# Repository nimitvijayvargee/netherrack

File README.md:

# netherrack
A Compute Module 5 Carrier board to use as a minecraft server!
This is a project that I made once the minecraft server plans began to leave the group chat. I initially planned on using it for minecraft, but the applications can vary from home server, NAS to photo server. \
I plan to use a CM5 board with 4GB RAM. While I did plan on using a no emmc and no wireless module, I had to go for a 32GB and Wireless module because of availability. \
I plan to use a 256GB NVMe SSD for storage, which can be swapped out because of the inbuilt M.2 PCIe port. \
I also plan on adding some IO including USB and HDMI for debug or when I want to use it as a desktop. \
The board is designed to be mounted vertically, with the ports on the side and an acrylic panel on the front, giving it a retro green motherboard with a modern front panel look. \

 \

# BOM
|Item            |Link                                                                          |Cost|
|----------------|------------------------------------------------------------------------------|----|
|PCB + Assembly  |https://pcbpower.com/                                                         |140 |
|USB Stacked Port|https://mou.sr/3H7Itof/                                                       |4   |
|Magjack port    |https://mou.sr/4lZehuO/                                                       |10  |
|CM5 4GB 32GB    |https://www.fabtolab.com/raspberry-pi-compute-module-5/                       |95  |
|Case            |Print Legion                                                                  |    |
|NVMe SSD        |https://www.amazon.in/EVM-Internal-1800MB-EVMNV-256GB/dp/B09F6DNLBD/          |21  |
|Mounting Screws |https://quartzcomponents.com/products/m2-5-25mm-bolt-mounting-screw-pack-of-4/|3   |
|Mounting Inserts|https://www.amazon.in/Pro3D-Brass-Threaded-Round-Insert/dp/B0CZ44JWF9/        |3   |
|Acrylic Panel   |https://robu.in/ (From self)                                                  |    |
|TOTAL           |                                                                              |276 |

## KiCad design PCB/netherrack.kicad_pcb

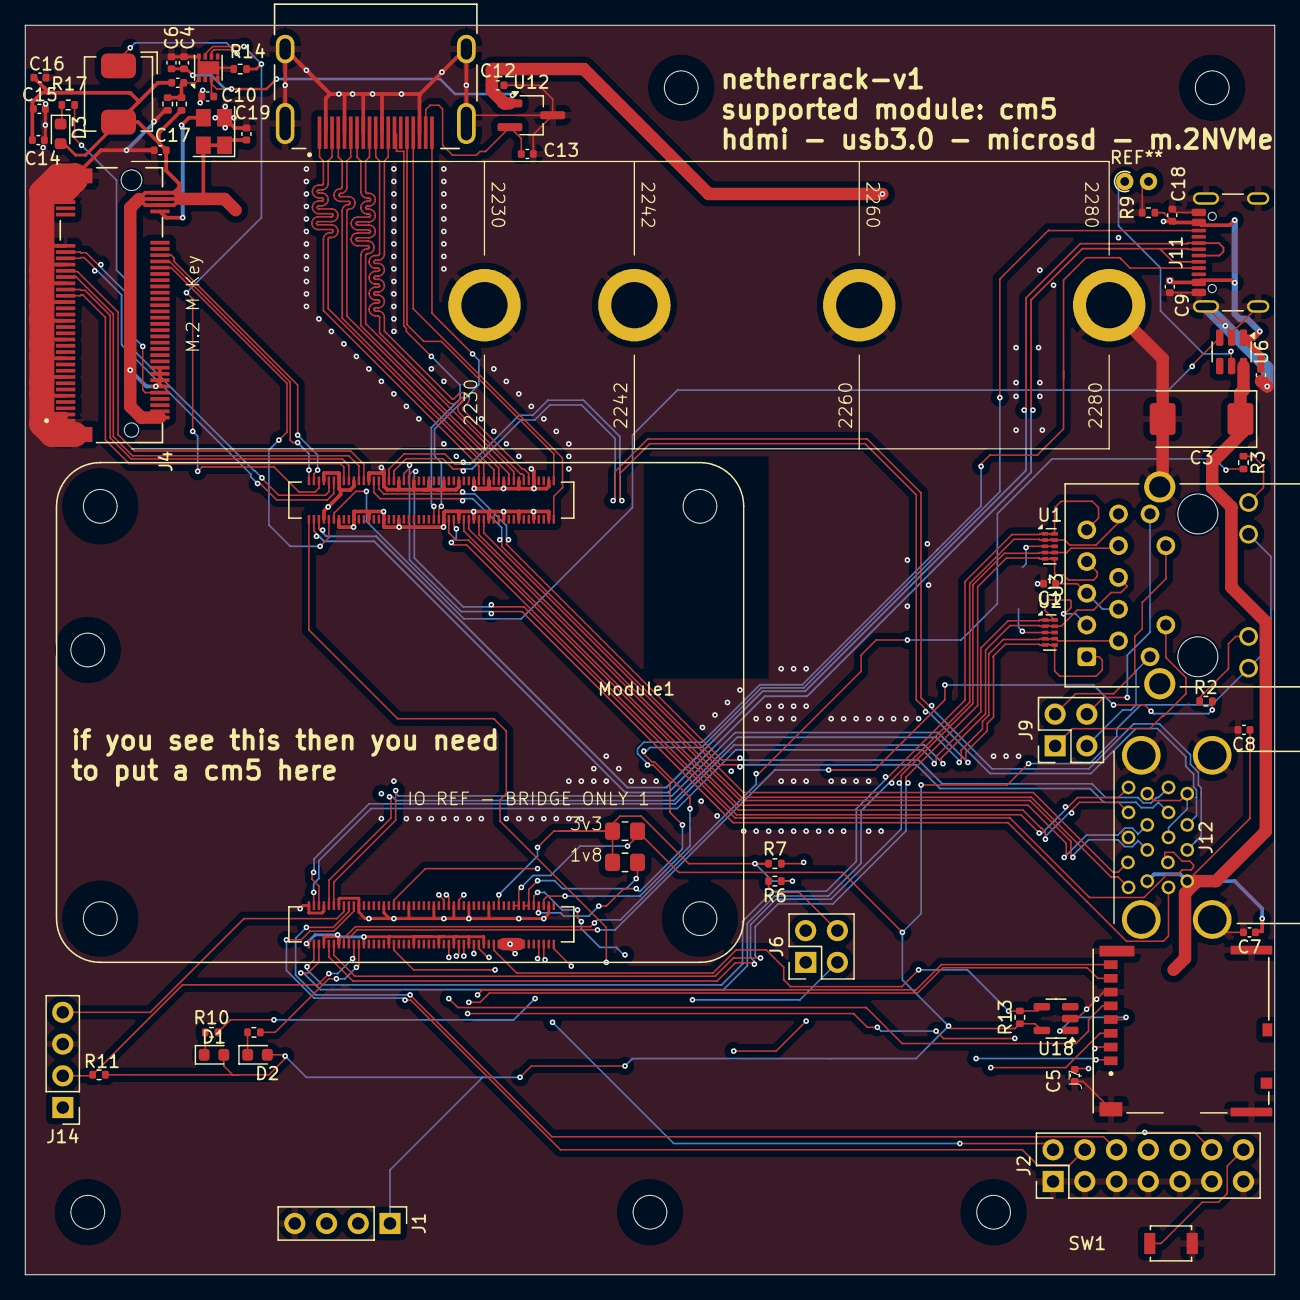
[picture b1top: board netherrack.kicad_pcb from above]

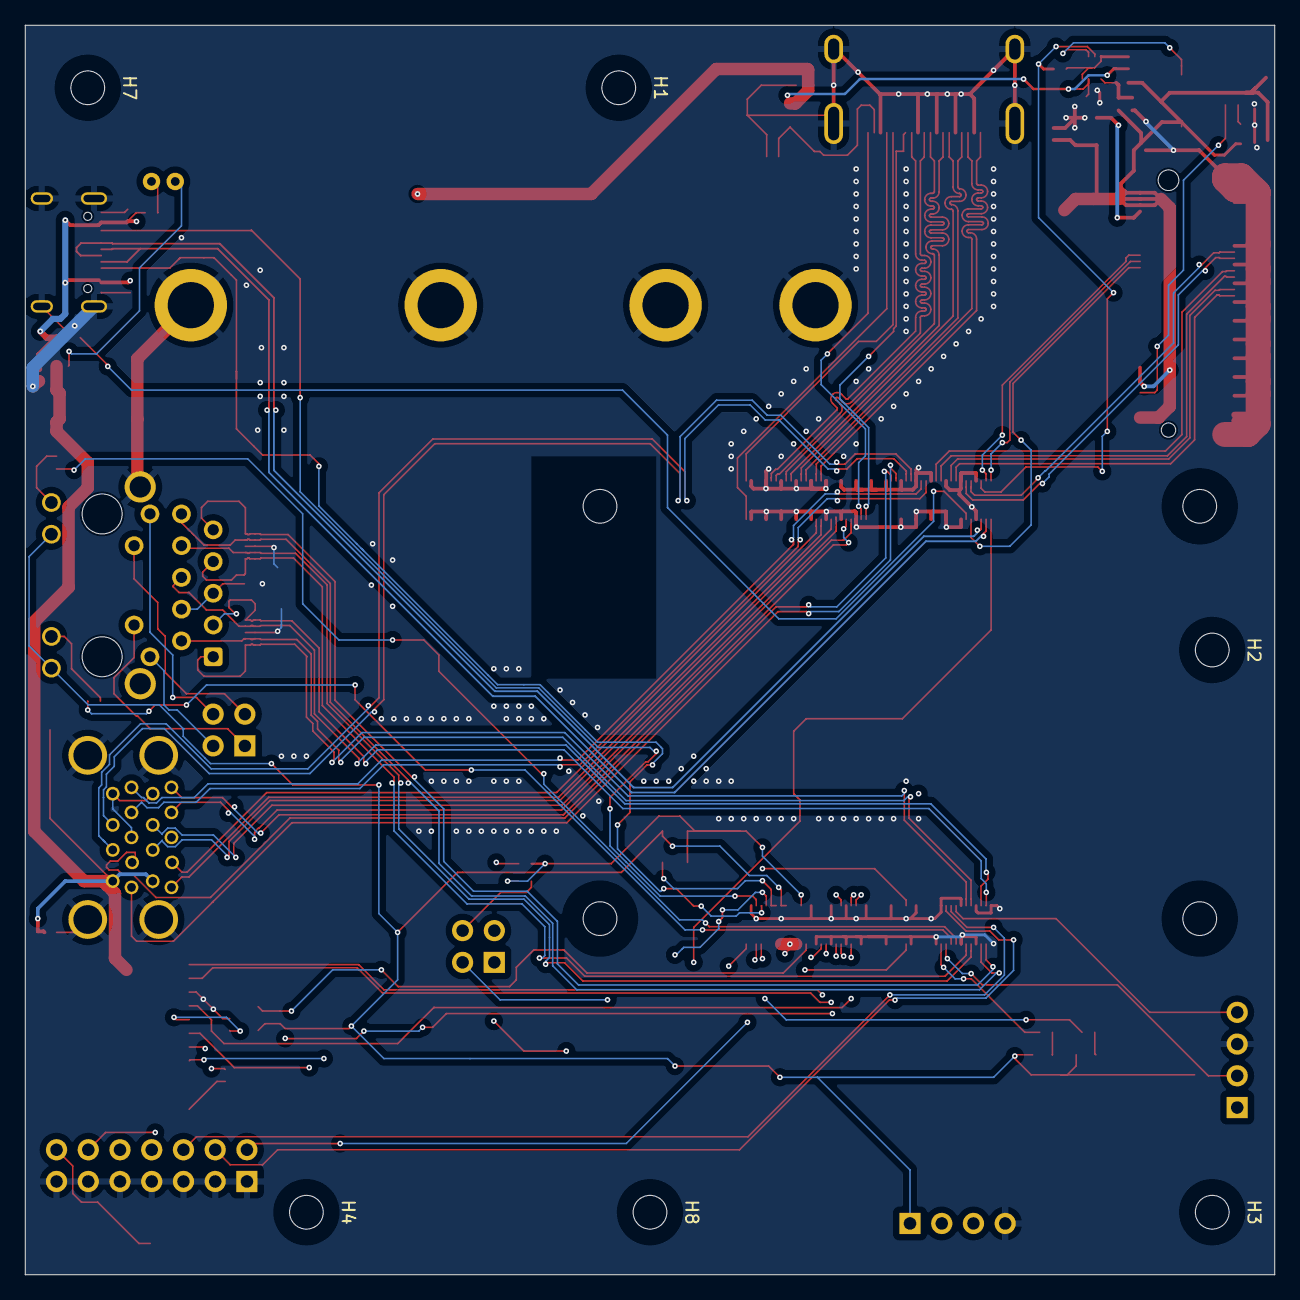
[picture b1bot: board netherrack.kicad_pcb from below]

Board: 4 copper layers, 100.0 x 100.0 mm, 64 parts (6 on the bottom side), 95 nets.

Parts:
C1, C9, C10, C12, C13, C18, C19: 100n; C_0402_1005Metric
C2, C4, C5, C6, C7, C8, C14, C15, C16, C17: 10u; C_0402_1005Metric
C3: 100uF; CP_EIA-7343-31_Kemet-D
C11: 4.7nF; C_0402_1005Metric
D1: LED Red; LED_0603_1608Metric
D2: LED Green; LED_0603_1608Metric
D3: LED; LED_0603_1608Metric
H1, H2, H3, H4, H7, H8: MountingHole; MountingHole_2.7mm_M2.5_DIN965
J1: Conn_01x04; PinHeader_1x04_P2.54mm_Vertical
J2: Conn_02x07_Odd_Even; PinHeader_2x07_P2.54mm_Vertical
J4: Bus_M.2_Socket_M; M.2 M Key socket
J6, J9: THD-02-R; PinHeader_2x02_P2.54mm_Vertical
J7: Micro_SD_Card_Det; SDCARD_MOLEX_503398-1892
J11: USB_C_Receptacle_USB2.0; USB_C_Receptacle_GCT_USB4105-xx-A_16P_TopMnt_Horizontal
J12: USB3_A; MTCONN_UBAF30-D2011
J14: JST_SHBM04B-SRSS-TB; PinHeader_1x04_P2.54mm_Vertical
J22: 690-019-298-412; EDAC 690-019-298-412
L1: 2.2uH; L_Bourns_SRP5030CC
Module1: ComputeModule5-CM5; Raspberry-Pi-5-Compute-Module
R1, R10, R17: 1k; R_0402_1005Metric
R2, R3: 470R; R_0402_1005Metric
R4: nf; R_0805_2012Metric_Pad1.20x1.40mm_HandSolder
R5: 0R; R_0805_2012Metric_Pad1.20x1.40mm_HandSolder
R6, R7, R9, R16: 2.2K 1%; R_0402_1005Metric
R11, R13, R15: 10K 1%; R_0402_1005Metric
R14: 100K 1%; R_0402_1005Metric
SW1: Right angle Tact button; SW_SPST_B3U-1000P
U1, U2: TPD4EUSB30; USON-10_2.5x1.0mm_P0.5mm
U3: MagJack-A70-112-331N126; TRJG0926HENL
U6: AP22653W6; SOT-23-6
U7: ASEK-32.768KHZ-L-R-T; Crystal_SMD_3225-4Pin_3.2x2.5mm
U8: AP3441SHE-7B; DFN-8-1EP_2x2mm_P0.5mm_EP1.05x1.75mm
U12: RT9742SNGV; TSOT-23_HandSoldering
U18: RT9742GGJ5; SOT-23-5

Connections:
/+3.3v: D1.2 (A), D2.2 (A), J1.1, Module1.84 (+3.3v_(Output)), Module1.86 (+3.3v_(Output)), R5.1, R11.1, R13.1, U3.15 (LEDY_A), U3.17 (LEDG_A), U18.5 (IN)
/+5v: C2.1, C4.1, C6.1, C9.1, C10.1, C12.1, C18.1, J11.A4 (VBUS), J11.A9 (VBUS), J11.B4 (VBUS), J11.B9 (VBUS), J14.1, Module1.77 (+5v_(Input)), Module1.79 (+5v_(Input)), Module1.81 (+5v_(Input)), Module1.83 (+5v_(Input)), Module1.85 (+5v_(Input)), Module1.87 (+5v_(Input)), R9.1, U6.1 (IN), U8.3 (VIN), U12.1 (IN)
/CC1: J11.A5 (CC1), Module1.94 (CC1)
/CC2: J11.B5 (CC2), Module1.96 (CC2)
/GPIO (Ethernet, SD_CARD for CM5L)/+1.8v: Module1.88 (+1.8v_(Output)), Module1.90 (+1.8v_(Output)), R4.1
/GPIO (Ethernet, SD_CARD for CM5L)/EEPROM_nWP: J2.4, Module1.20 (EEPROM_nWP)
/GPIO (Ethernet, SD_CARD for CM5L)/ETH_LEDG: Module1.17 (Ethernet_nLED2(3.3v)), R2.2
/GPIO (Ethernet, SD_CARD for CM5L)/ETH_LEDY: Module1.15 (Ethernet_nLED3(3.3v)), R3.2
/GPIO (Ethernet, SD_CARD for CM5L)/GPIO2: J1.2, Module1.58 (GPIO2)
/GPIO (Ethernet, SD_CARD for CM5L)/GPIO3: J1.3, Module1.56 (GPIO3)
/GPIO (Ethernet, SD_CARD for CM5L)/GPIO_VREF: Module1.78 (GPIO_VREF(1.8v/3.3v_Input)), R4.2, R5.2, R6.1, R7.1
/GPIO (Ethernet, SD_CARD for CM5L)/ID_SC: J6.1, Module1.35 (ID_SC)
/GPIO (Ethernet, SD_CARD for CM5L)/ID_SD: J6.3, Module1.36 (ID_SD)
/GPIO (Ethernet, SD_CARD for CM5L)/PMIC_ENABLE: J2.12, Module1.99 (PMIC_ENABLE)
/GPIO (Ethernet, SD_CARD for CM5L)/PWM: J14.2, Module1.19 (FAN_PWM), R11.2
/GPIO (Ethernet, SD_CARD for CM5L)/PWR_BUT: J2.14, Module1.92 (PWR_BUT), SW1.1
/GPIO (Ethernet, SD_CARD for CM5L)/SD_CLK: J7.5 (CLK), Module1.57 (SD_CLK)
/GPIO (Ethernet, SD_CARD for CM5L)/SD_CMD: J7.3 (CMD), Module1.62 (SD_CMD)
/GPIO (Ethernet, SD_CARD for CM5L)/SD_DAT0: J7.7 (DAT0), Module1.63 (SD_DAT0)
/GPIO (Ethernet, SD_CARD for CM5L)/SD_DAT1: J7.8 (DAT1), Module1.67 (SD_DAT1)
/GPIO (Ethernet, SD_CARD for CM5L)/SD_DAT2: J7.1 (DAT2), Module1.69 (SD_DAT2)
/GPIO (Ethernet, SD_CARD for CM5L)/SD_DAT3: J7.2 (DAT3/CD), Module1.61 (SD_DAT3)
/GPIO (Ethernet, SD_CARD for CM5L)/SD_PWR: C5.1, J7.4 (VDD), U18.1 (OUT)
/GPIO (Ethernet, SD_CARD for CM5L)/SD_PWR_ON: Module1.75 (SD_PWR_ON), R13.2, U18.4 (EN)
/GPIO (Ethernet, SD_CARD for CM5L)/SYNC_OUT: J2.6, Module1.18 (Ethernet_SYNC_OUT(3.3v))
/GPIO (Ethernet, SD_CARD for CM5L)/TACHO: J14.4, Module1.16 (FAN_TACHO)
/GPIO (Ethernet, SD_CARD for CM5L)/TR0_TAP: J9.3, U3.11 (VC1)
/GPIO (Ethernet, SD_CARD for CM5L)/TR1_TAP: J9.1, U3.12 (VC2)
/GPIO (Ethernet, SD_CARD for CM5L)/TR2_TAP: J9.2, U3.13 (VC3)
/GPIO (Ethernet, SD_CARD for CM5L)/TR3_TAP: J9.4, U3.14 (VC4)
/GPIO (Ethernet, SD_CARD for CM5L)/TRD0_N: Module1.10 (Ethernet_Pair0_N), U2.4 (D2+), U2.7, U3.2 (TRD0-)
/GPIO (Ethernet, SD_CARD for CM5L)/TRD0_P: Module1.12 (Ethernet_Pair0_P), U2.5 (D2-), U2.6, U3.1 (TRD0+)
/GPIO (Ethernet, SD_CARD for CM5L)/TRD1_N: Module1.6 (Ethernet_Pair1_N), U2.2 (D1-), U2.9, U3.6 (TRD1-)
/GPIO (Ethernet, SD_CARD for CM5L)/TRD1_P: Module1.4 (Ethernet_Pair1_P), U2.1 (D1+), U2.10, U3.3 (TRD1+)
/GPIO (Ethernet, SD_CARD for CM5L)/TRD2_N: Module1.9 (Ethernet_Pair2_N), U1.4 (D2+), U1.7, U3.8 (TRD2-)
/GPIO (Ethernet, SD_CARD for CM5L)/TRD2_P: Module1.11 (Ethernet_Pair2_P), U1.5 (D2-), U1.6, U3.7 (TRD2+)
/GPIO (Ethernet, SD_CARD for CM5L)/TRD3_N: Module1.5 (Ethernet_Pair3_N), U1.2 (D1-), U1.9, U3.10 (TRD3-)
/GPIO (Ethernet, SD_CARD for CM5L)/TRD3_P: Module1.3 (Ethernet_Pair3_P), U1.1 (D1+), U1.10, U3.9 (TRD3+)
/GPIO (Ethernet, SD_CARD for CM5L)/USBOTG: J2.10, Module1.101 (USB_OTG_ID)
/GPIO (Ethernet, SD_CARD for CM5L)/nPWR_LED: Module1.95 (LED_nPWR), R10.2
/GPIO (Ethernet, SD_CARD for CM5L)/nRPIBOOT: J2.2, Module1.93 (nRPIBOOT)
/Highspeed (USB, HDMI)/HDMI0_CEC: J22.13 (CEC), Module1.151 (HDMI0_CEC)
/Highspeed (USB, HDMI)/HDMI0_CK_N: J22.12 (CK-), Module1.190 (HDMI0_CLK_N)
/Highspeed (USB, HDMI)/HDMI0_CK_P: J22.10 (CK+), Module1.188 (HDMI0_CLK_P)
/Highspeed (USB, HDMI)/HDMI0_D0_N: J22.9 (D0-), Module1.184 (HDMI0_TX0_N)
/Highspeed (USB, HDMI)/HDMI0_D0_P: J22.7 (D0+), Module1.182 (HDMI0_TX0_P)
/Highspeed (USB, HDMI)/HDMI0_D1_N: J22.6 (D1-), Module1.178 (HDMI0_TX1_N)
/Highspeed (USB, HDMI)/HDMI0_D1_P: J22.4 (D1+), Module1.176 (HDMI0_TX1_P)
/Highspeed (USB, HDMI)/HDMI0_D2_N: J22.3 (D2-), Module1.172 (HDMI0_TX2_N)
/Highspeed (USB, HDMI)/HDMI0_D2_P: J22.1 (D2+), Module1.170 (HDMI0_TX2_P)
/Highspeed (USB, HDMI)/HDMI0_HOTPLUG: J22.19 (HPD/HEAC-), Module1.153 (HDMI0_HOTPLUG)
/Highspeed (USB, HDMI)/HDMI0_SCL: J22.15 (SCL), Module1.200 (HDMI0_SCL)
/Highspeed (USB, HDMI)/HDMI0_SDA: J22.16 (SDA), Module1.199 (HDMI0_SDA)
/Highspeed (USB, HDMI)/HDMI_5v: C13.1, J22.18 (+5V), U12.2 (OUT)
/Highspeed (USB, HDMI)/PCIE_CLK_N: J4.53 (REFCLKn), Module1.112 (PCIe_CLK_N)
/Highspeed (USB, HDMI)/PCIE_CLK_P: J4.55 (REFCLKp), Module1.110 (PCIe_CLK_P)
/Highspeed (USB, HDMI)/PCIE_PWR_EN: Module1.106 (PCIE_PWR_EN), R14.1, U8.7 (EN)
/Highspeed (USB, HDMI)/PCIE_RX_N: J4.43 (PETp0), Module1.118 (PCIe_RX_N)
/Highspeed (USB, HDMI)/PCIE_RX_P: J4.41 (PETn0), Module1.116 (PCIe_RX_P)
/Highspeed (USB, HDMI)/PCIE_TX_N: J4.49 (PERp0), Module1.124 (PCIe_TX_N)
/Highspeed (USB, HDMI)/PCIE_TX_P: J4.47 (PERn0), Module1.122 (PCIe_TX_P)
/Highspeed (USB, HDMI)/PCIE_nCLKREQ: J4.52 (~CLKREQ), Module1.102 (PCIe_nCLKREQ)
/Highspeed (USB, HDMI)/PCIE_nRST: J4.50 (~PERST), Module1.109 (PCIe_nRST)
/Highspeed (USB, HDMI)/PCIE_nWAKE: J4.54 (~PEWAKE), Module1.104 (PCIE_nWAKE)
/Highspeed (USB, HDMI)/SCL1: J6.2, R7.2
/Highspeed (USB, HDMI)/SDA1: J6.4, R6.2
/Highspeed (USB, HDMI)/USB3-0-D_N: J12.A2 (D-), Module1.136 (USB3-0-D_N)
/Highspeed (USB, HDMI)/USB3-0-D_P: J12.A3 (D+), Module1.134 (USB3-0-D_P)
/Highspeed (USB, HDMI)/USB3-0-RX_N: J12.A6 (SSRX+), Module1.128 (USB3-0-RX_N)
/Highspeed (USB, HDMI)/USB3-0-RX_P: J12.A5 (SSRX-), Module1.130 (USB3-0-RX_P)
/Highspeed (USB, HDMI)/USB3-0-TX_N: J12.A9 (SSTX+), Module1.140 (USB3-0-TX_N)
/Highspeed (USB, HDMI)/USB3-0-TX_P: J12.A8 (SSTX-), Module1.142 (USB3-0-TX_P)
/Highspeed (USB, HDMI)/USB3-1-D_N: J12.B2 (D-), Module1.165 (USB3-1-D_N)
/Highspeed (USB, HDMI)/USB3-1-D_P: J12.B3 (D+), Module1.163 (USB3-1-D_P)
/Highspeed (USB, HDMI)/USB3-1-RX_N: J12.B6 (SSRX+), Module1.157 (USB3-1-RX_N)
/Highspeed (USB, HDMI)/USB3-1-RX_P: J12.B5 (SSRX-), Module1.159 (USB3-1-RX_P)
/Highspeed (USB, HDMI)/USB3-1-TX_N: J12.B9 (SSTX+), Module1.169 (USB3-1-TX_N)
/Highspeed (USB, HDMI)/USB3-1-TX_P: J12.B8 (SSTX-), Module1.171 (USB3-1-TX_P)
/Highspeed (USB, HDMI)/VBUS: C3.1, C7.1, C8.1, J12.A1 (VBUS), J12.B1 (VBUS), U6.6 (OUT)
/Highspeed (USB, HDMI)/VBUS_EN: Module1.111 (VBUS_EN), U6.3 (EN)
/PCIe-M2/FB: C11.2, R15.2, R16.1, U8.1 (FB)
/PCIe-M2/M2_3v3: C11.1, C14.1, C15.1, C16.1, C17.1, C19.1, D3.2 (A), J4.2 (3.3V), J4.4 (3.3V), J4.12 (3.3V), J4.14 (3.3V), J4.16 (3.3V), J4.18 (3.3V), J4.70 (3.3V), J4.72 (3.3V), J4.74 (3.3V), L1.2, R15.1, U7.1 (EN), U7.4 (VDD)
/USB2_N: J11.A7 (D-), J11.B7 (D-), Module1.103 (USB2_N)
/USB2_P: J11.A6 (D+), J11.B6 (D+), Module1.105 (USB2_P)
GND: C1.2, C2.2, C3.2, C4.2, C5.2, C6.2, C7.2, C8.2, C9.2, C10.2, C12.2, C13.2, C14.2, C15.2, C16.2, C17.2, C18.2, C19.2, J1.4, J2.1, J2.3, J2.5, J2.7, J2.9, J2.11, J2.13, J4.1 (GND), J4.3 (GND), J4.9 (GND), J4.15 (GND), J4.21 (GND), J4.27 (GND), J4.33 (GND), J4.39 (GND), J4.45 (GND), J4.51 (GND), J4.57 (GND), J4.71 (GND), J4.73 (GND), J4.75 (GND), J4.M1 (GND2230), J4.M2 (GND2242), J4.M3 (GND2260), J4.M4 (GND2280), J4.S1, J4.S2, J7.6 (VSS), J7.11 (SHIELD), J11.A1 (GND), J11.A12 (GND), J11.B1 (GND), J11.B12 (GND), J11.S1 (SHIELD), J12.10 (SHIELD), J12.A4 (GND), J12.A7 (DRAIN), J12.B4 (GND), J12.B7 (DRAIN), J14.3, J22.2 (D2S), J22.5 (D1S), J22.8 (D0S), J22.11 (CKS), J22.17 (GND), J22.SH1 (SH), J22.SH2 (SH), J22.SH3 (SH), J22.SH4 (SH), Module1.1 (GND), Module1.2 (GND), Module1.7 (GND), Module1.8 (GND), Module1.13 (GND), Module1.14 (GND), Module1.22 (GND), Module1.23 (GND), Module1.32 (GND), Module1.33 (GND), Module1.42 (GND), Module1.43 (GND), Module1.52 (GND), Module1.53 (GND), Module1.59 (GND), Module1.60 (GND), Module1.65 (GND), Module1.66 (GND), Module1.71 (GND), Module1.74 (GND), Module1.98 (GND), Module1.107 (GND), Module1.108 (GND), Module1.113 (GND), Module1.114 (GND), Module1.119 (GND), Module1.120 (GND), Module1.125 (GND), Module1.126 (GND), Module1.131 (GND), Module1.132 (GND), Module1.137 (GND), Module1.138 (GND), Module1.144 (GND), Module1.150 (GND), Module1.155 (GND), Module1.156 (GND), Module1.161 (GND), Module1.162 (GND), Module1.167 (GND), Module1.168 (GND), Module1.173 (GND), Module1.174 (GND), Module1.179 (GND), Module1.180 (GND), Module1.185 (GND), Module1.186 (GND), Module1.191 (GND), Module1.192 (GND), Module1.197 (GND), Module1.198 (GND), R9.2, R14.2, R16.2, SW1.2, U1.3 (GND), U1.8 (GND), U2.3 (GND), U2.8 (GND), U3.19 (SHIELD), U3.20 (SHIELD), U6.2 (GND), U7.2 (GND), U8.4 (PGND), U8.8 (SGND), U8.9 (PAD), U12.3 (GND), U18.2 (GND)
unnamed: C1.1, U3.4 (CT), U3.5 (CT)
unnamed: D1.1 (K), R10.1
unnamed: D2.1 (K), R1.1
unnamed: D3.1 (K), R17.1
unnamed: J4.10 (DAS/~DSS/~LED1), R17.2
unnamed: J4.68 (SUSCLK), U7.3 (Out)
unnamed: Module1.21 (LED_nACT), R1.2
unnamed: R3.1, U3.18 (LEDG_K)
unnamed: R2.1, U3.16 (LEDY_K)
unnamed: L1.1, U8.6 (LX)

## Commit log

2025-07-27 Journal + PCB
2025-07-28 Update completed PCB
2025-07-30 Submission commit
2025-07-30 Fix dates
2025-07-30 Fix time spent
